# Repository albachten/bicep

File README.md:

# Bicep - Flexing my "ARM" muscles

This is a simple ARM Cortex M0 development board with:
* SAMD21 cpu
* 2 serial connectors
* 915MHz Hope RFM95 Lora module
* LiPo battery w/usb charger and on-off switch
* 3 I2C connectors (2 QWIIC and one pin header)

[Schematic pdf](v1.0.bicep.pdf)

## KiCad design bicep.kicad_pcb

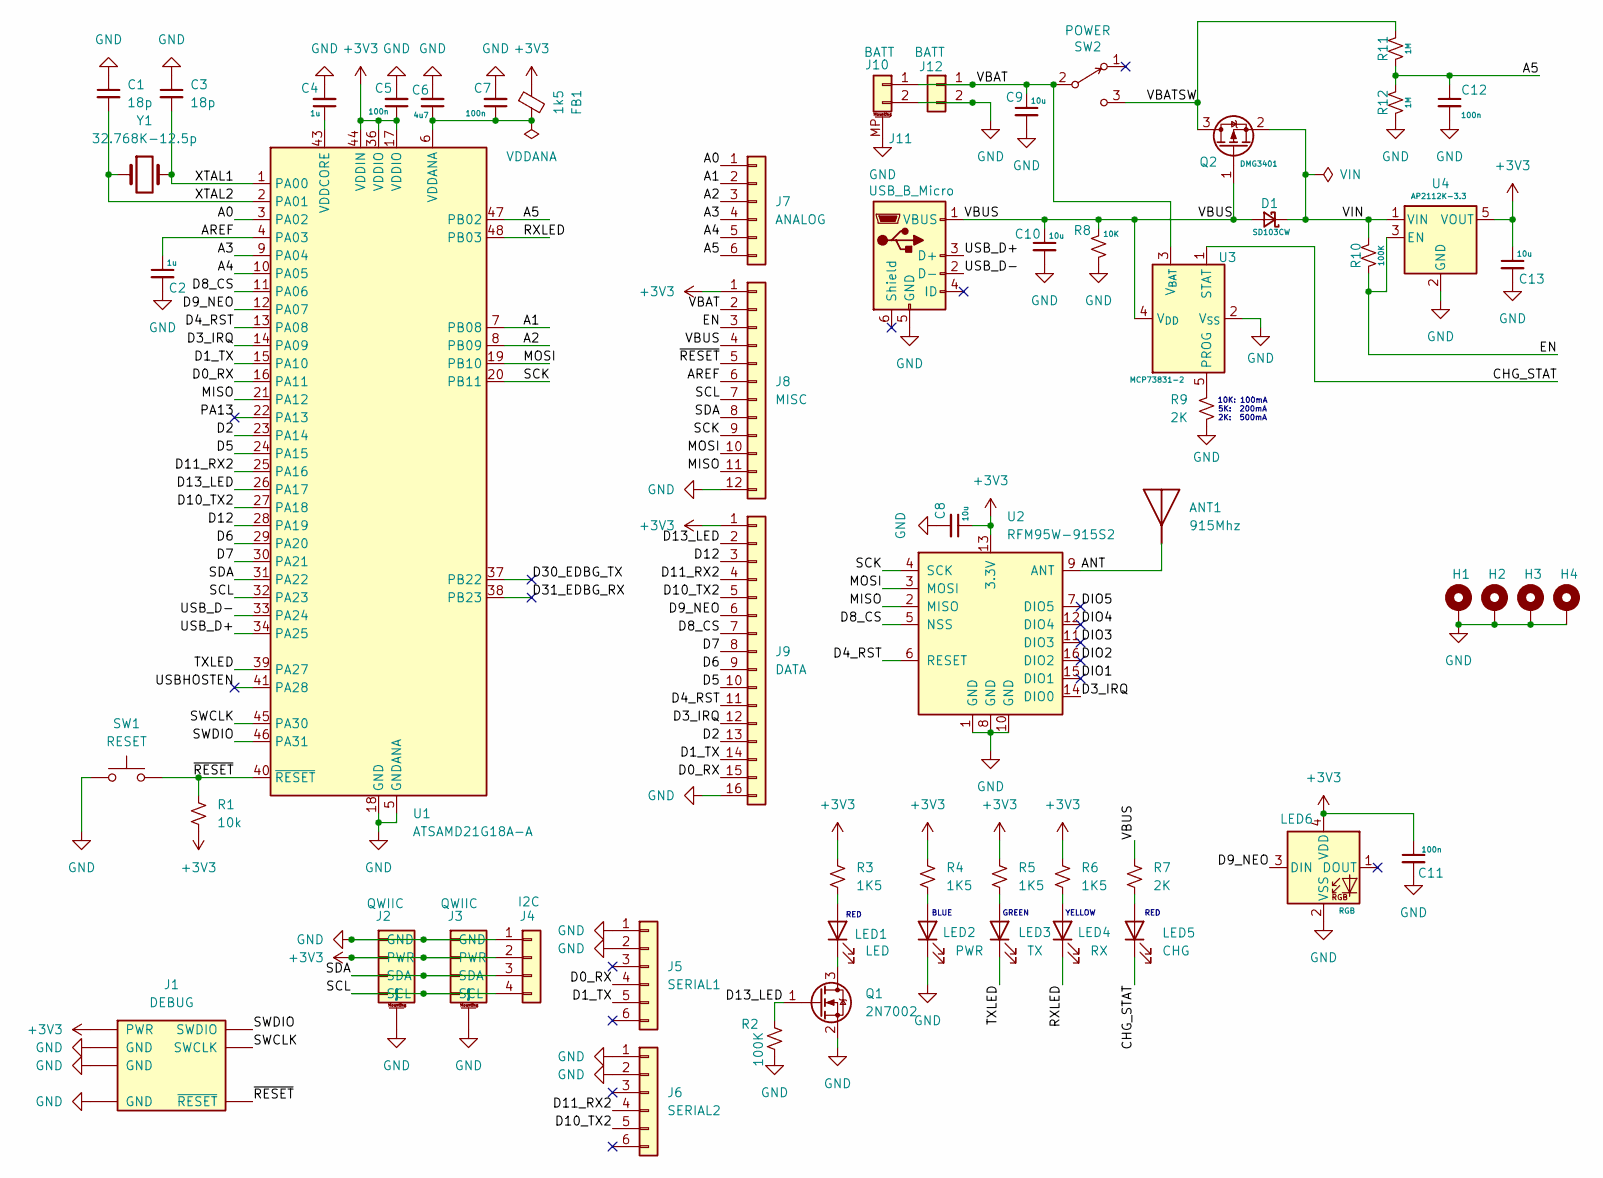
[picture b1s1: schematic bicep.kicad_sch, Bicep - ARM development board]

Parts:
ANT1: 915Mhz; Texas_SWRA416_868MHz_915MHz
C1, C3: 18p; C_0805_2012Metric
C2, C4: 1u; C_0805_2012Metric
C5, C7, C11, C12: 100n; C_0805_2012Metric
C6: 4u7; C_0805_2012Metric
C8, C9, C10, C13: 10u; C_0805_2012Metric
D1: SD103CW; D_SOD-123
FB1: 1k5; L_0805_2012Metric
H1, H2, H3, H4: MountingHole_Pad; MountingHole_3.2mm_M3_ISO7380_Pad
J1: DEBUG; CortexDebug
J2, J3: QWIIC; QWIIC_JST_SH_BM04B-SRSS-TB_1x04-1MP_P1.00mm_Vertical
J4: I2C; PinHeader_1x04_P2.54mm_Vertical
J5: SERIAL1; PinHeader_1x06_P2.54mm_Vertical
J6: SERIAL2; PinHeader_1x06_P2.54mm_Vertical
J7: ANALOG; PinHeader_1x06_P2.54mm_Vertical
J8: MISC; PinHeader_1x12_P2.54mm_Vertical
J9: DATA; PinHeader_1x16_P2.54mm_Vertical
J10: BATT; JST_PH_S2B-PH-SM4-TB_1x02-1MP_P2.00mm_Horizontal
J11: USB_B_Micro; USB_Micro-B_Amphenol_10118194_Horizontal
J12: BATT; PinHeader_1x02_P2.54mm_Vertical
LED1: LED; LED_0805_2012Metric
LED2: PWR; LED_0805_2012Metric
LED3: TX; LED_0805_2012Metric
LED4: RX; LED_0805_2012Metric
LED5: CHG; LED_0805_2012Metric
LED6: RGB; LED_WS2812B-2020_PLCC4_2.0x2.0mm
Q1: 2N7002; SOT-23
Q2: DMG3401; SOT-23
R1: 10k; R_0805_2012Metric
R2, R10: 100K; R_0805_2012Metric
R3, R4, R5, R6: 1K5; R_0805_2012Metric
R7, R9: 2K; R_0805_2012Metric
R8: 10K; R_0805_2012Metric
R11, R12: 1M; R_0805_2012Metric
SW1: RESET; TL3305B_SPST_PushButton
SW2: POWER; EG1218_SPDT_Slide_Switch
U1: ATSAMD21G18A-A; TQFP-48_7x7mm_P0.5mm
U2: RFM95W-915S2; RFM95CW
U3: MCP73831-2; SOT-23-5
U4: AP2112K-3.3; SOT-23-5
Y1: 32.768K-12.5p; Crystal_SMD_G8-2Pin_3.2x1.5mm

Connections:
+3V3: C5.1, C8.1, C11.1, C13.1, FB1.1, J1.1 (PWR), J2.2 (PWR), J3.2 (PWR), J4.2, J8.1, J9.1, LED6.4 (VDD), R1.2, R3.1, R4.1, R5.1, R6.1, U1.17 (VDDIO), U1.36 (VDDIO), U1.44 (VDDIN), U2.13 (3.3V), U4.5 (VOUT)
/A0: J7.1, U1.3 (PA02)
/A1: J7.2, U1.7 (PB08)
/A2: J7.3, U1.8 (PB09)
/A3: J7.4, U1.9 (PA04)
/A4: J7.5, U1.10 (PA05)
/A5: C12.1, J7.6, R11.1, R12.2, U1.47 (PB02)
/ANT: ANT1.1 (A), U2.9 (ANT)
/AREF: C2.1, J8.6, U1.4 (PA03)
/CHG_STAT: LED5.1 (K), U3.1 (STAT)
/D0_RX: J5.4, J9.15, U1.16 (PA11)
/D1_TX: J5.5, J9.14, U1.15 (PA10)
/D2: J9.13, U1.23 (PA14)
/D3_IRQ: J9.12, U1.14 (PA09), U2.14 (DIO0)
/D4_RST: J9.11, U1.13 (PA08), U2.6 (RESET)
/D5: J9.10, U1.24 (PA15)
/D6: J9.9, U1.29 (PA20)
/D7: J9.8, U1.30 (PA21)
/D8_CS: J9.7, U1.11 (PA06), U2.5 (NSS)
/D9_NEO: J9.6, LED6.3 (DIN), U1.12 (PA07)
/D10_TX2: J6.5, J9.5, U1.27 (PA18)
/D11_RX2: J6.4, J9.4, U1.25 (PA16)
/D12: J9.3, U1.28 (PA19)
/D13_LED: J9.2, Q1.1 (G), R2.1, U1.26 (PA17)
/D30_EDBG_TX: U1.37 (PB22)
/D31_EDBG_RX: U1.38 (PB23)
/DIO1: U2.15 (DIO1)
/DIO2: U2.16 (DIO2)
/DIO3: U2.11 (DIO3)
/DIO4: U2.12 (DIO4)
/DIO5: U2.7 (DIO5)
/EN: J8.3, R10.1, U4.3 (EN)
/MISO: J8.11, U1.21 (PA12), U2.2 (MISO)
/MOSI: J8.10, U1.19 (PB10), U2.3 (MOSI)
/PA13: U1.22 (PA13)
/RXLED: LED4.1 (K), U1.48 (PB03)
/SCK: J8.9, U1.20 (PB11), U2.4 (SCK)
/SCL: J2.4 (SCL), J3.4 (SCL), J4.4, J8.7, U1.32 (PA23)
/SDA: J2.3 (SDA), J3.3 (SDA), J4.3, J8.8, U1.31 (PA22)
/SWCLK: J1.4 (SWCLK), U1.45 (PA30)
/SWDIO: J1.2 (SWDIO), U1.46 (PA31)
/TXLED: LED3.1 (K), U1.39 (PA27)
/USBHOSTEN: U1.41 (PA28)
/USB_D+: J11.3 (D+), U1.34 (PA25)
/USB_D-: J11.2 (D-), U1.33 (PA24)
/VBAT: C9.1, J8.2, J10.1, J12.1, SW2.2 (B), U3.3 (V_{BAT})
/VBATSW: Q2.3 (D), R11.2, SW2.3 (C)
/VBUS: C10.1, D1.2 (A), J8.4, J11.1 (VBUS), Q2.1 (G), R7.1, R8.2, U3.4 (V_{DD})
/VIN: D1.1 (K), Q2.2 (S), R10.2, U4.1 (VIN)
/XTAL1: C3.2, U1.1 (PA00), Y1.2
/XTAL2: C1.2, U1.2 (PA01), Y1.1
/~RESET: J1.10 (~RESET), J8.5, R1.1, SW1.2, U1.40 (~RESET)
GND: C1.1, C2.2, C3.1, C4.2, C5.2, C6.2, C7.2, C8.2, C9.2, C10.2, C11.2, C12.2, C13.2, H1.1, H2.1, H3.1, H4.1, J1.3 (GND), J1.5 (GND), J1.9 (GND), J2.1 (GND), J2.MP (MountPin), J3.1 (GND), J3.MP (MountPin), J4.1, J5.1, J5.2, J6.1, J6.2, J8.12, J9.16, J10.2, J10.MP (MountPin), J11.5 (GND), J12.2, LED2.1 (K), LED6.2 (VSS), Q1.2 (S), R2.2, R8.1, R9.2, R12.1, SW1.1, U1.5 (GNDANA), U1.18 (GND), U1.35 (GND), U1.42 (GND), U2.1 (GND), U2.8 (GND), U2.10 (GND), U3.2 (V_{SS}), U4.2 (GND)
unnamed: LED1.2 (A), R3.2
unnamed: LED1.1 (K), Q1.3 (D)
unnamed: LED2.2 (A), R4.2
unnamed: LED3.2 (A), R5.2
unnamed: LED4.2 (A), R6.2
unnamed: LED5.2 (A), R7.2
unnamed: C6.1, C7.1, FB1.2, U1.6 (VDDANA)
unnamed: C4.1, U1.43 (VDDCORE)
unnamed: R9.1, U3.5 (PROG)

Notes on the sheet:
BLUE
GREEN
YELLOW
10K: 100mA 5K: 200mA 2K: 500mA
RED

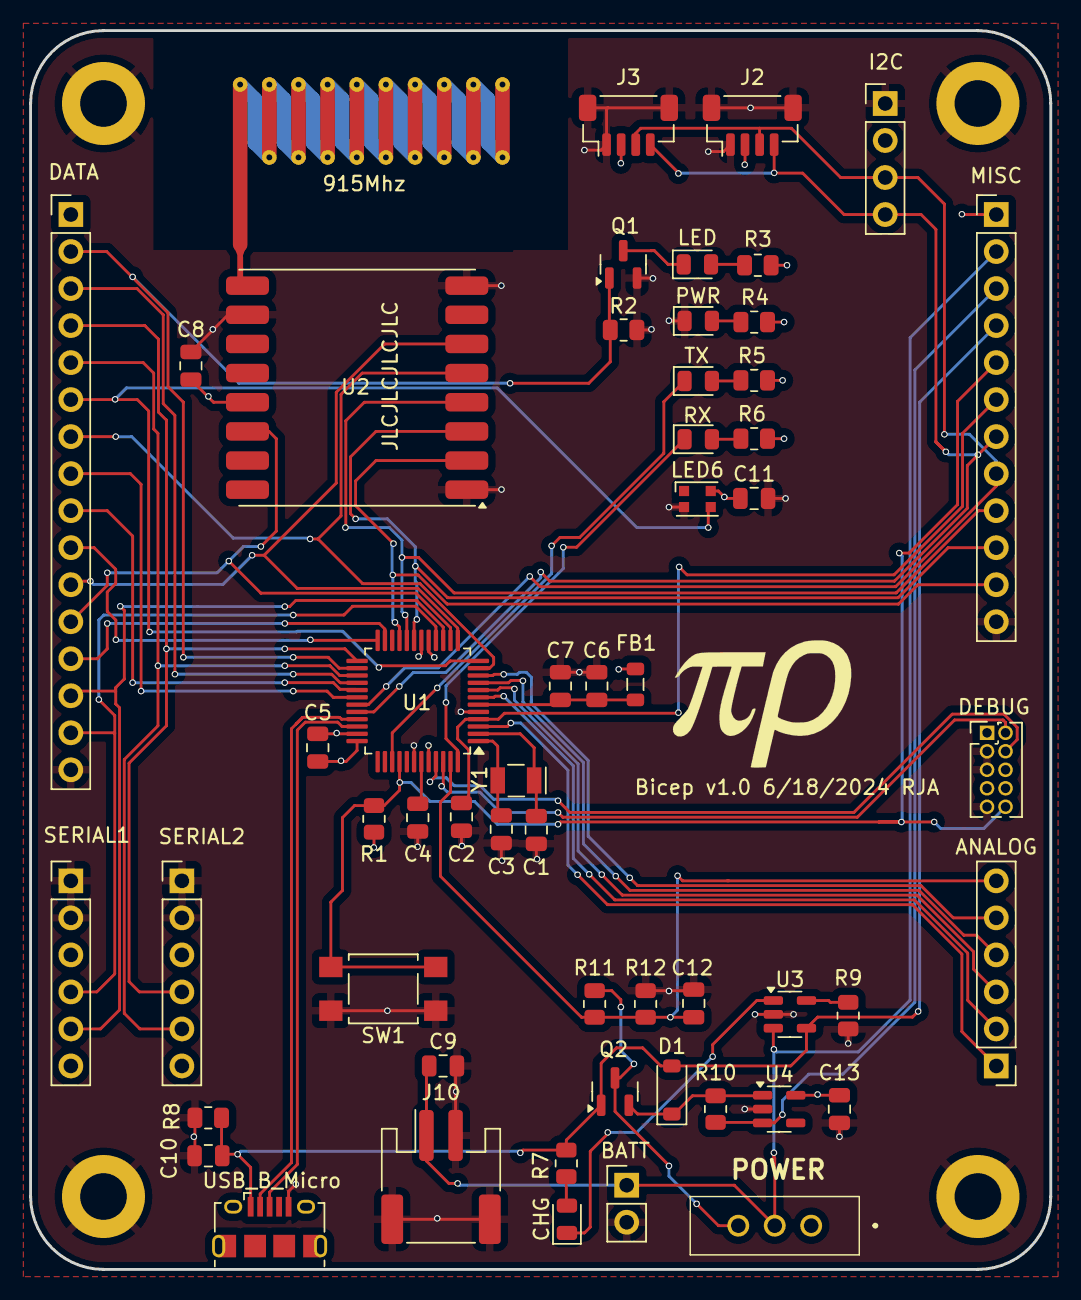
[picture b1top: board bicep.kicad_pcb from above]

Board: 4 copper layers, 70.0 x 85.0 mm, 59 parts (0 on the bottom side), 53 nets.

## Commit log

2024-06-19 v1.0 initial commit
2024-06-19 Added shroud to 3d rendering of Cortex Debug connector
